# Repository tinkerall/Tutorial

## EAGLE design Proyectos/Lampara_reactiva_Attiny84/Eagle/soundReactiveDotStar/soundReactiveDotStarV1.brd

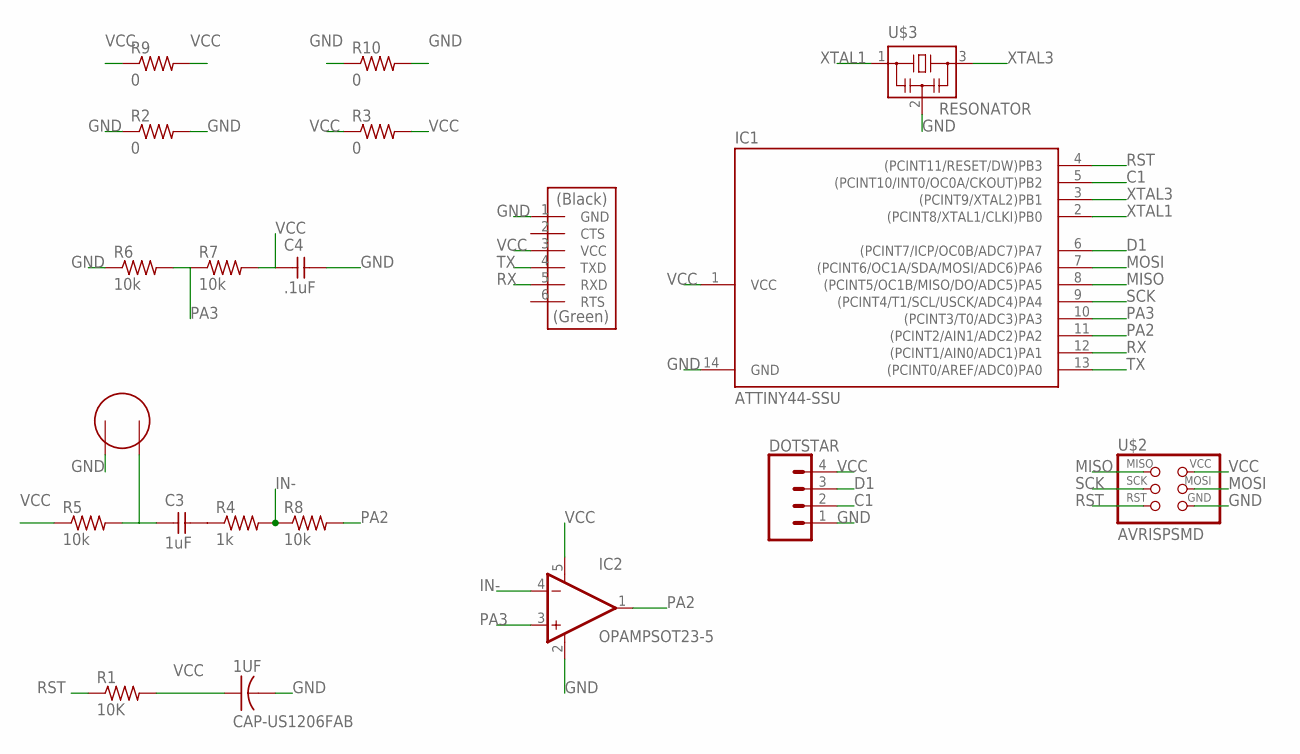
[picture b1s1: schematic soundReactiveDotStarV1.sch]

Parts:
1UF: CAP-US1206FAB; C1206FAB
C3: 1uF; C1206FAB
C4: .1uF; C1206FAB
DOTSTAR: CONN_04SMD_RA_FEMALE; 1X04_SMD_RA_FEMALE
IC1: ATTINY44-SSU; SOIC14
IC2: OPAMPSOT23-5; SOT23-5
R1: 10K; R1206FAB
R2, R3, R9, R10: 0; R1206FAB
R4: 1k; R1206FAB
R5, R6, R7, R8: 10k; R1206FAB
U$1: FTDI-SMD-HEADER; 1X06SMD
U$2: AVRISPSMD; 2X03SMD
U$3: RESONATOR; EFOBM
U$4: ELECTRET; ELECTRET_2742PBJ-A

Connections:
C1: DOTSTAR.2, IC1.5 ((PCINT10/INT0/OC0A/CKOUT)PB2)
D1: DOTSTAR.3, IC1.6 ((PCINT7/ICP/OC0B/ADC7)PA7)
GND: 1UF.2, C4.2, DOTSTAR.1, IC1.14 (GND), IC2.2 (V-), R2.1, R2.2, R6.1, R10.1, R10.2, U$1.1 (GND), U$2.6 (GND), U$3.2, U$4.P$1
IN-: IC2.4 (-IN), R4.2, R8.1
MISO: IC1.8 ((PCINT5/OC1B/MISO/DO/ADC5)PA5), U$2.1 (MISO)
MOSI: IC1.7 ((PCINT6/OC1A/SDA/MOSI/ADC6)PA6), U$2.4 (MOSI)
unnamed: C3.1, R5.2, U$4.P$2
unnamed: C3.2, R4.1
PA2: IC1.11 ((PCINT2/AIN1/ADC2)PA2), IC2.1 (OUT), R8.2
PA3: IC1.10 ((PCINT3/T0/ADC3)PA3), IC2.3 (+IN), R6.2, R7.1
RST: IC1.4 ((PCINT11/RESET/DW)PB3), R1.1, U$2.5 (RST)
RX: IC1.12 ((PCINT1/AIN0/ADC1)PA1), U$1.5 (RXD)
SCK: IC1.9 ((PCINT4/T1/SCL/USCK/ADC4)PA4), U$2.3 (SCK)
TX: IC1.13 ((PCINT0/AREF/ADC0)PA0), U$1.4 (TXD)
VCC: 1UF.1, C4.1, DOTSTAR.4, IC1.1 (VCC), IC2.5 (V+), R1.2, R3.1, R3.2, R5.1, R7.2, R9.1, R9.2, U$1.3 (VCC), U$2.2 (VCC)
XTAL1: IC1.2 ((PCINT8/XTAL1/CLKI)PB0), U$3.1
XTAL3: IC1.3 ((PCINT9/XTAL2)PB1), U$3.3

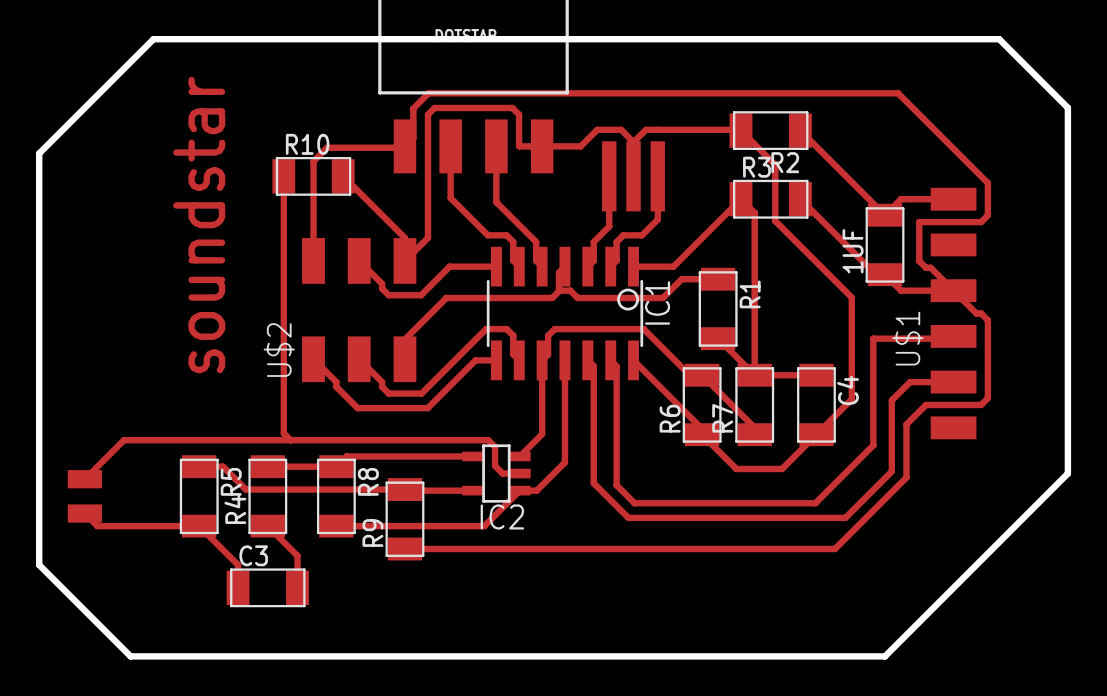
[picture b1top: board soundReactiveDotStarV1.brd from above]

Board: 2 copper layers, 57.1 x 34.3 mm, 20 parts (0 on the bottom side), 17 nets.

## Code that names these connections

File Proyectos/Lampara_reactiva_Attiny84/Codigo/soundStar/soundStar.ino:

/*
  Author: Elena C. K.
  Description: Attiny84 to control DotStar LED strip from Adafruit. It only have enough byte to control approximately 32 LEDs.
  Use the FastLED library to program.
  IDE Attiny84 Physical Pin
  0      PA0           13 - TX
  1      PA1           12 - RX
  2      PA2           11 - OPAMP OUT
  3      PA3           10
  4      PA4            9
  5      PA5            8
  6      PA6            7
  7      PA7            6 - D1
  8      PB2            5 - C1
  9      PB1            3
  10     PB0           2
*/

#include <FastLED.h>
#define LED_DT 7                                             // Serial data pin
#define LED_CK 8                                             // Serial clock pin for APA102 or WS2801
#define COLOR_ORDER BGR                                       // It's GRB for WS2812B
#define LED_TYPE APA102                                       // What kind of strip are you using (APA102, WS2801 or WS@2812B
#define NUM_LEDS 72
#define MIC 2
#define DC_OFFSET 512

#include <SoftwareSerial.h>
#define RX 1
#define TX 0
CRGB leds[NUM_LEDS];
SoftwareSerial Serial(TX, RX);

uint8_t max_bright = 128;                                      // Overall brightness definition. It can be changed on the fly.

// Colours defined for below
long firstval = 0xff00ff;
CRGB rgbval(50,0,500);
CHSV hsvval(100,255,200);
uint8_t startpos = 0;
int endpos = NUM_LEDS-1;

uint8_t thishue = 0;
uint8_t deltahue = 15;

void setup() {
  Serial.begin(57600);
  FastLED.clear();
  //  LEDS.addLeds<LED_TYPE, LED_DT, COLOR_ORDER>(leds, NUM_LEDS);       // Use this for WS2812B
  LEDS.addLeds<LED_TYPE, LED_DT, LED_CK, COLOR_ORDER>(leds, NUM_LEDS); // Use this for APA102 or WS2801

  FastLED.setBrightness(max_bright);
  set_max_power_in_volts_and_milliamps(5, 500);

  pinMode(MIC, INPUT);
}

void loop() {
  int sample = 0;                                            // Current sample. Starts with negative values, which is why it's signed.
  sample = analogRead(MIC) - DC_OFFSET;
  sample = abs(sample);
//  Serial.println(sample);
//  delay(100);

//FORWARD_HUES, BACKWARD_HUES, SHORTEST_HUES, LONGEST_HUES
//  fill_gradient(leds, startpos, CHSV(50, 255,255) , endpos, CHSV(150,255,255), SHORTEST_HUES);
  if(sample >= 18){
    sample =18;
  }
  fill_gradient(leds, 4*sample , CHSV(50, 255,255), CHSV(100,255,255), LONGEST_HUES);    // up to 4 CHSV values

// fill_rainbow section
//  fill_rainbow(leds, 20+NUM_LEDS/(NUM_LEDS-10*sample), thishue, deltahue);            // Use FastLED's fill_rainbow routine.
//  fill_solid(leds,NUM_LEDS,0);                                // Clear the strip for. . . 
//  fill_rainbow(leds+1, NUM_LEDS-2, thishue, deltahue);        // One pixel border at each end.

  FastLED.show();                         // Power managed display
  delay(30);
}

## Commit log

2016-09-10 Joystick tutorial
2016-09-13 Update joystick and relay programs
2016-11-15 pir sensor
2016-11-17 ultrasonico tutorial basico
2016-12-07 Episodio 3 y las imagenes
2017-01-11 Código de serie de tutoriales para arduino básico
2017-01-11 fixed double files
2017-01-12 updated ep8 code
2017-04-26 Codigo del episodio 11
2017-04-26 circuit
2018-01-11 EP13
2018-01-17 codigo Episodio 14
2018-01-24 sensor ultrasonico tutorial
2018-01-31 tutorial ep16
2019-02-03 Lampara reactiva al sonido

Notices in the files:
parts and their libraries:
SparkFun-Connectors: Licensing: Creative Commons ShareAlike 4.0 International - https://creativecommons.org/licenses/by-sa/4.0
